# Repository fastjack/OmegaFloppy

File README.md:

# ΩFloppy

A modernized version of XUM1541 with USB-C. Based on the design of the [ZoomFloppy](https://github.com/go4retro/ZoomFloppy) but stripped of all the "weird" connectors.

## Images

Yes, I am aware that the two pins of the DIN connector do not line up with the footprint. This is a problem with Lumberg's CAD model (I contacted them about it). I have [verified](images/footprint-test.jpeg) the footprint with the real connector.

## WARNING!
This PCB is still untested. First PCBs have been ordered.

This KiCAD project was created with a nightly build of KiCAD 10.99. The current release of KiCAD 10 (Version 10.0.6 as of this writing) will most certainly not open the project.

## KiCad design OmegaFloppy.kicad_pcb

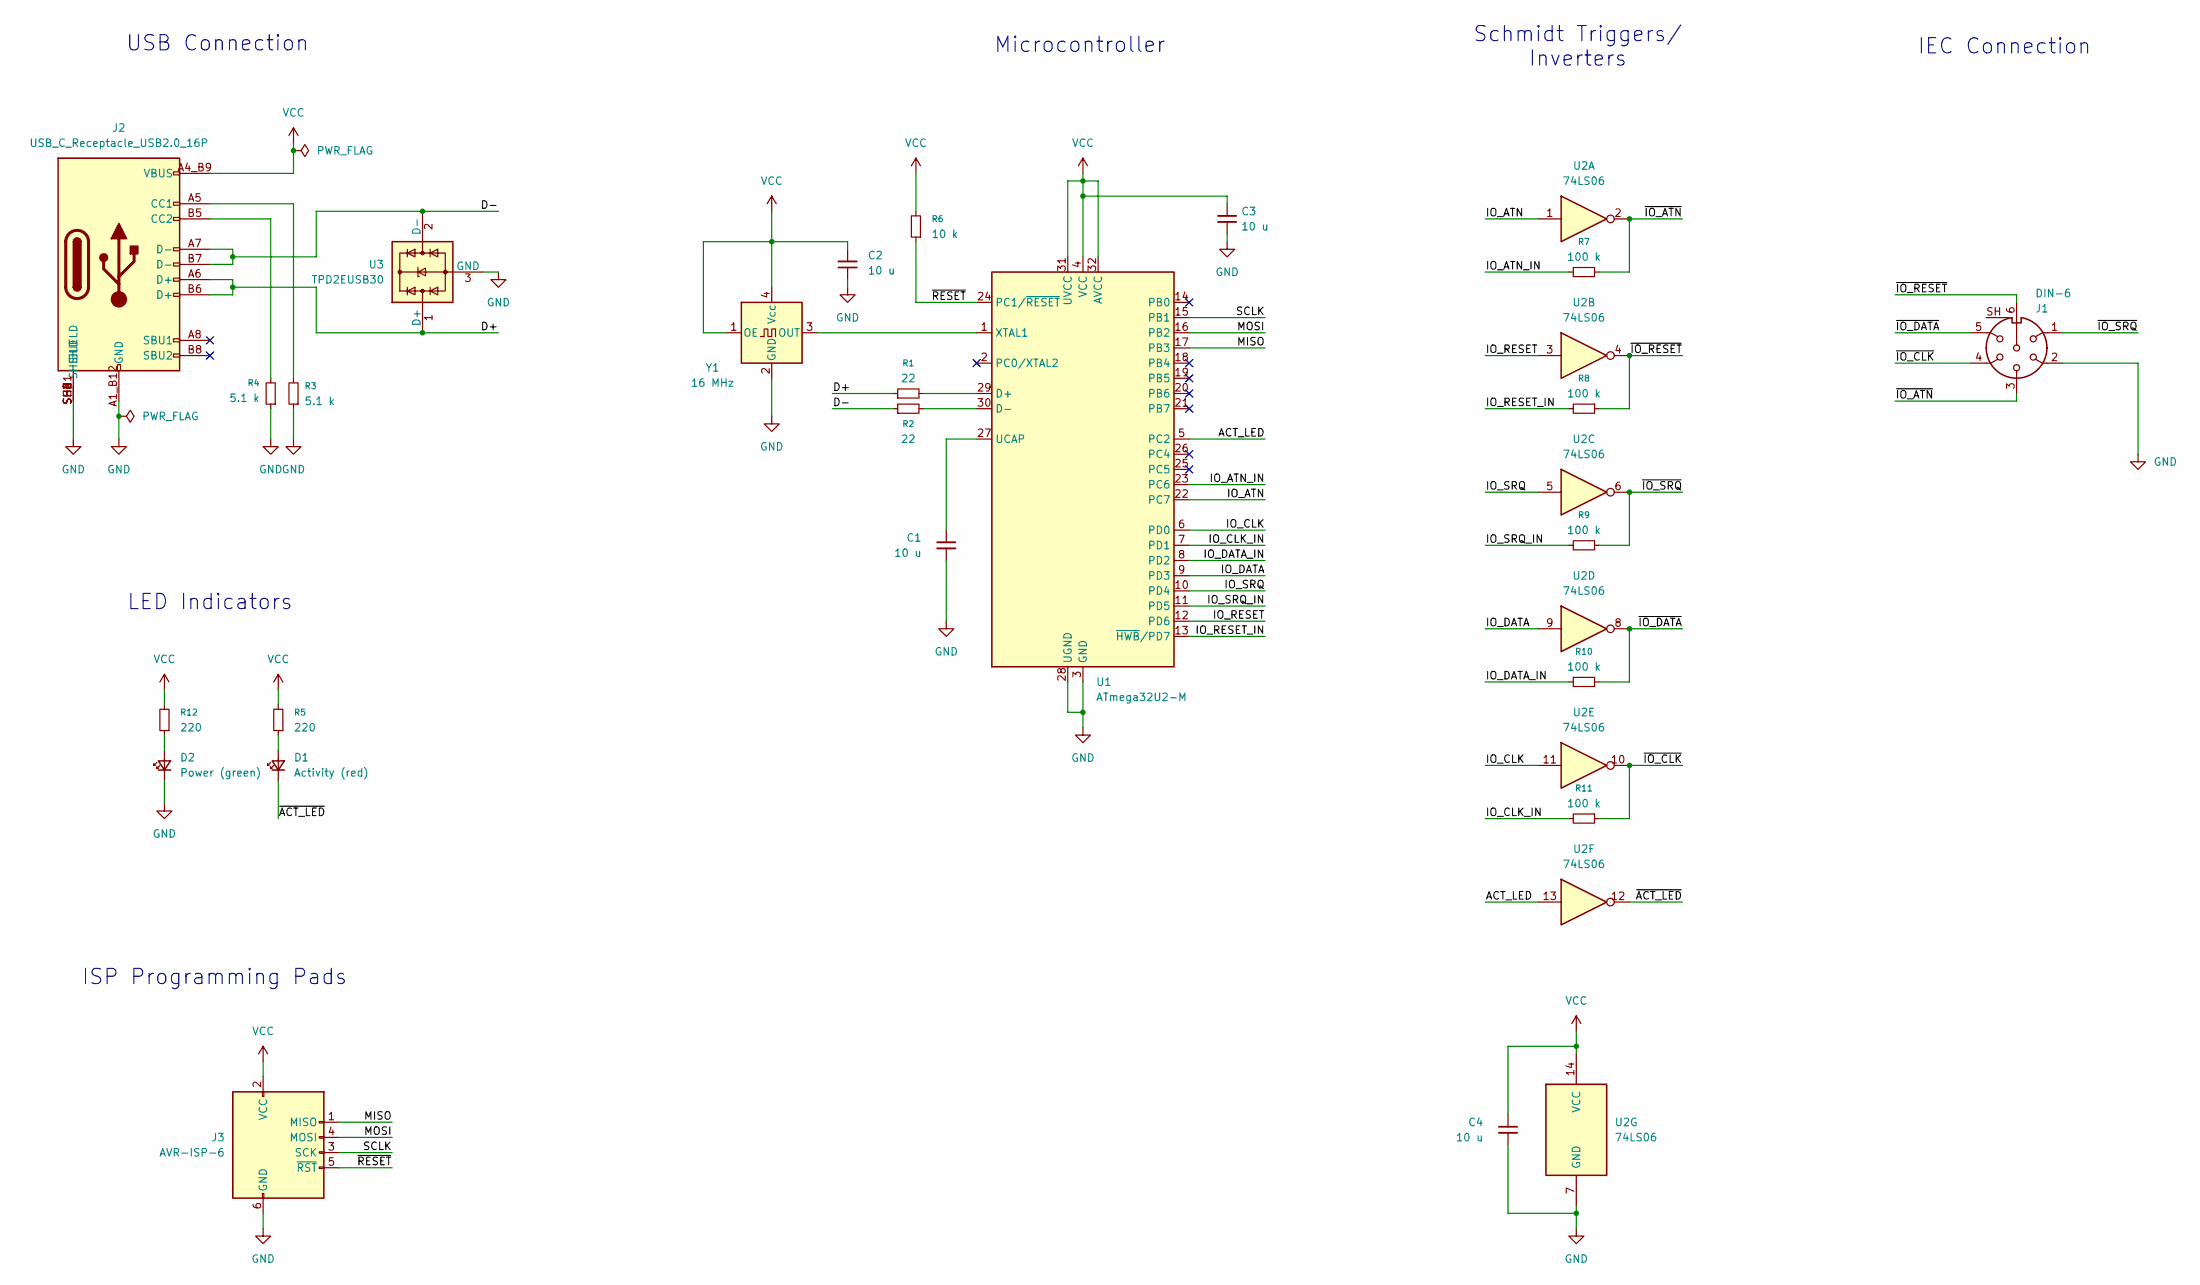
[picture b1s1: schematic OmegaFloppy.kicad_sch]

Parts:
C1, C2, C3, C4: 10 u; C_0402_1005Metric; MPN GRM155R61A106ME11D; LCSC C408132
D1: Activity (red); LED_0402_1005Metric; MPN IN-S42DS5R; LCSC C6968971
D2: Power (green); LED_0402_1005Metric; MPN IN-S42DS5G; LCSC C6968971
J1: DIN-6; DIN45322; MPN 0105 06
J2: USB_C_Receptacle_USB2.0_16P; AMPHENOL_10155435-00011LF; MPN 10155435-00011LF; LCSC C5409177
J3: AVR-ISP-6; AVRISP_Pogo
R1, R2: 22; R_0402_1005Metric; MPN RK73H1ETTP22R0F; LCSC C159964
R3, R4: 5.1 k; R_0402_1005Metric; MPN RN73R1ETTP5101B25; LCSC C2480097
R5, R12: 220; R_0402_1005Metric; MPN RN73R1ETTP2200F50; LCSC C2499122
R6: 10 k; R_0402_1005Metric; MPN RN73R1ETTP1002B25; LCSC C2480096
R7, R8, R9, R10, R11: 100 k; R_0402_1005Metric; MPN RN73R1ETTP1003B25; LCSC C2480096
U1: ATmega32U2-M; QFN-32-1EP_5x5mm_P0.5mm_EP3.1x3.1mm; MPN ATMEGA32U2-MU; LCSC C57345
U2: 74LS06; SSOP-14_5.3x6.2mm_P0.65mm; MPN SN74LS06DBR; LCSC C2682072
U3: TPD2EUSB30; Texas_DRT-3; MPN TPD2EUSB30ADRTR; LCSC C94934
Y1: 16 MHz; Crystal_SMD_3225-4Pin_3.2x2.5mm; MPN SX3M16.000A10F20TNN; LCSC C41361431

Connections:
/ACT_LED: U1.5 (PC2), U2.13
/D+: J2.A6 (D+), J2.B6 (D+), R1.1, U3.1 (D+)
/D-: J2.A7 (D-), J2.B7 (D-), R2.1, U3.2 (D-)
/IO_ATN: U1.22 (PC7), U2.1
/IO_ATN_IN: R7.2, U1.23 (PC6)
/IO_CLK: U1.6 (PD0), U2.11
/IO_CLK_IN: R11.2, U1.7 (PD1)
/IO_DATA: U1.9 (PD3), U2.9
/IO_DATA_IN: R10.2, U1.8 (PD2)
/IO_RESET: U1.12 (PD6), U2.3
/IO_RESET_IN: R8.2, U1.13 (~HWB/PD7)
/IO_SRQ: U1.10 (PD4), U2.5
/IO_SRQ_IN: R9.2, U1.11 (PD5)
/MISO: J3.1 (MISO), U1.17 (PB3)
/MOSI: J3.4 (MOSI), U1.16 (PB2)
/SCLK: J3.3 (SCK), U1.15 (PB1)
/~ACT_LED: D1.1 (K), U2.12
/~IO_ATN: J1.3, R7.1, U2.2
/~IO_CLK: J1.4, R11.1, U2.10
/~IO_DATA: J1.5, R10.1, U2.8
/~IO_RESET: J1.6, R8.1, U2.4
/~IO_SRQ: J1.1, R9.1, U2.6
/~RESET: J3.5 (~RST), R6.1, U1.24 (PC1/~RESET)
GND: C1.2, C2.2, C3.2, C4.2, D2.1 (K), J1.2, J2.A1_B12 (GND), J2.B1_A12 (GND), J2.SH1 (SHIELD), J2.SH2 (SHIELD), J2.SH3 (SHIELD), J2.SH4 (SHIELD), J3.6 (GND), R3.1, R4.1, U1.3 (GND), U1.28 (UGND), U1.33 (GND), U2.7 (GND), U3.3 (GND), Y1.2 (GND)
unnamed: D1.2 (A), R5.1
unnamed: D2.2 (A), R12.1
unnamed: J2.A5 (CC1), R3.2
unnamed: J2.B5 (CC2), R4.2
unnamed: R1.2, U1.29 (D+)
unnamed: R2.2, U1.30 (D-)
unnamed: C1.1, U1.27 (UCAP)
unnamed: U1.1 (XTAL1), Y1.3 (OUT)
VCC: C2.1, C3.1, C4.1, J2.A4_B9 (VBUS), J2.B4_A9 (VBUS), J3.2 (VCC), R5.2, R6.2, R12.2, U1.4 (VCC), U1.31 (UVCC), U1.32 (AVCC), U2.14 (VCC), Y1.1 (OE), Y1.4 (Vcc)

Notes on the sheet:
LED Indicators
ISP Programming Pads
USB Connection
Schmidt Triggers/ Inverters
IEC Connection
Microcontroller

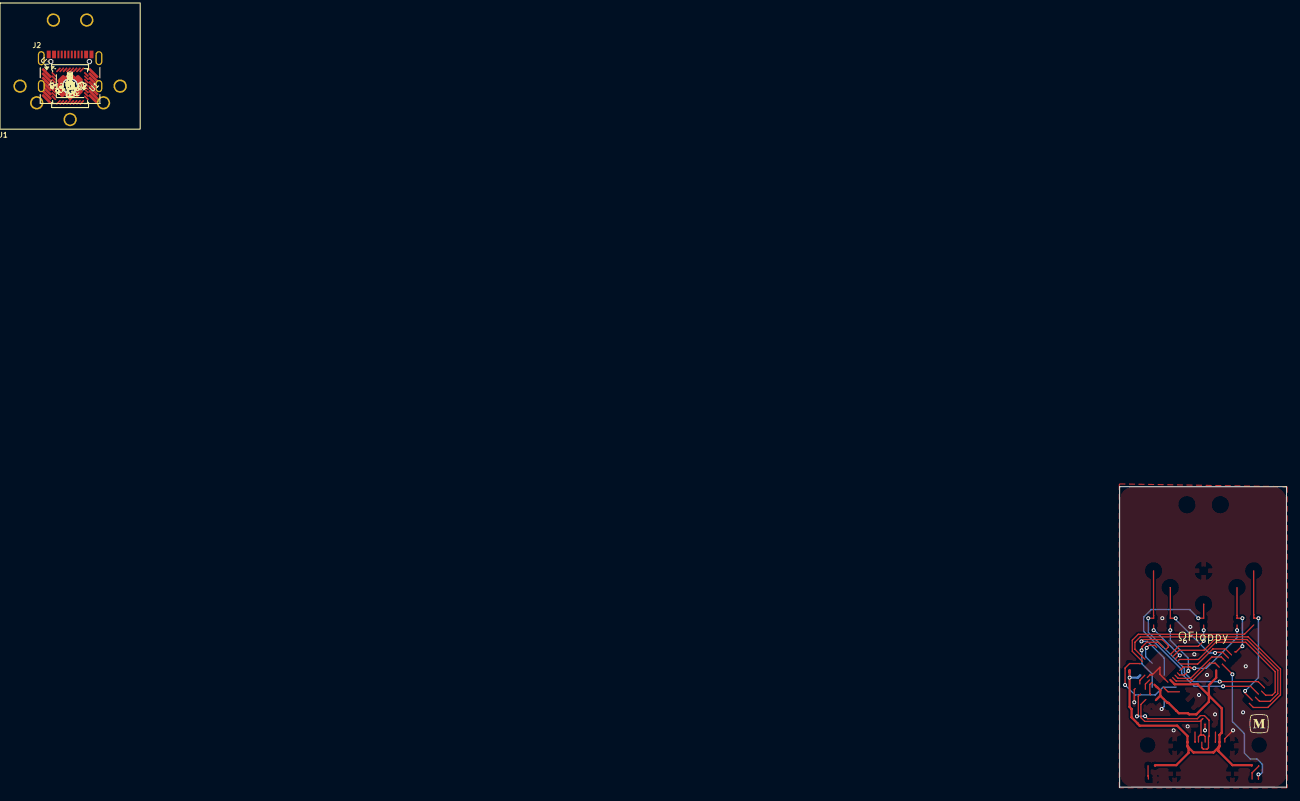
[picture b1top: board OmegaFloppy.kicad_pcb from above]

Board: 2 copper layers, 25.0 x 45.0 mm, 25 parts (1 on the bottom side), 33 nets.
